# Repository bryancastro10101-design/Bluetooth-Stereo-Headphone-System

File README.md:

# 🎧 Bluetooth Stereo Headphone System
**EE 445L Embedded System Design Lab — Final Project | The University of Texas at Austin**

A fully functional wireless stereo audio system built from scratch using an ESP32 and TM4C123 microcontroller, featuring real-time DSP, dual TFT displays, and a custom PCB designed in KiCad.

---

## 📌 Project Overview

This project demonstrates end-to-end embedded system design — from hardware architecture and PCB layout to firmware development and digital signal processing. Audio is streamed wirelessly from a PC via Bluetooth (A2DP protocol), decoded by an ESP32, and transmitted over SPI to a TM4C123 microcontroller for processing and playback through dual speakers.

---

## 🏗️ System Architecture

```
[PC / Spotify]
     │
     │  Bluetooth A2DP
     ▼
[ESP32 DevKitC]  ──── SPI ────►  [TM4C123GH6PM]
                                       │
                          ┌────────────┴────────────┐
                          │                         │
                     [TLV5616 DAC]           [TLV5616 DAC]
                          │                         │
                    [MCP34119 OPA]           [MCP34119 OPA]
                          │                         │
                      [Speaker L]             [Speaker R]
                          
         [ST7735R LCD ×2]  ◄── SPI ── TM4C123
         [Volume Buttons ×4]
```

**Communication Protocols:**
- **Bluetooth A2DP** — Wireless audio streaming from PC to ESP32
- **SPI** — ESP32 → TM4C123 audio data transfer; TM4C123 → DACs and LCD screens
- **I2C** — ESP32 ↔ TM4C123 control/status channel

---

## ⚙️ Hardware Components

| Component | Part | Qty | Role |
|---|---|---|---|
| Microcontroller | TM4C123GH6PM | 1 | Main audio processor |
| Wireless MCU | ESP32-DevKitC-V4 | 1 | Bluetooth A2DP receiver |
| TFT Display | ST7735R | 2 | Real-time audio level UI |
| DAC | TLV5616 | 2 | Digital-to-analog conversion |
| Op-Amp | MCP34119P | 2 | Audio amplification |
| Buck Regulator | MPM3610GQV | 2 | 9V → 5V and 9V → 3.3V |
| Voltage Reference | LM4041CILPR | 1 | Stable DAC reference |

---

## 🔋 Power Budget

| Rail | Load Breakdown | Range |
|---|---|---|
| **3.3V** | TM4C123 + 2× ST7735R + ESP32 + regulators + Vref | 231 mA – 321 mA |
| **5V** | 2× MCP34119 + 2× TLV5616 | ~2.32 mA |

Both rails are supplied by MPM3610GQV switching regulators from a 9V source, chosen for their high efficiency and small footprint.

---

## 💻 Firmware Design

### ESP32 — Bluetooth Receiver
Receives audio data over Bluetooth A2DP and streams it to the TM4C123 via SPI as fast as data is available.

```c
// ESP32 pseudocode
int main() {
    while (true) {
        while (SoundDataReady) {
            SPIOut(SoundData);
        }
    }
    return 0;
}
```

### TM4C123 — Audio Processor
Acts as the SPI slave, processes incoming audio data, and distributes it to the two DAC channels and both LCD displays.

**Module structure:**
```
dac.h       → DAC_Init(), DAC_Output(uint16_t data)
slave.h     → Slave_Init(void (*handler)(uint8_t databyte))
speaker.h   → init_Speaker(), play_Sound(int soundData)
lcd.h       → init_LCD(), update_LCD(update_Params params)
```

---

## 🖥️ User Interface

- **2× ST7735R TFT displays** showing real-time audio level visualization that responds dynamically to volume
- **4 buttons** (2 per channel) for:
  - Volume control (up/down)
  - Equalization adjustment

---

## 📐 PCB Design

Designed in **KiCad** targeting **JLCPCB** manufacturing rules.

**Key design decisions:**
- Regulators placed close to the battery connector to minimize long power traces
- Speaker/Amp/DAC subcircuit routed once and mirrored for the stereo channel
- Booster pack headers spaced for TM4C123 LaunchPad compatibility
- Crystal oscillator isolated from high-speed signal traces

---

## 📊 Performance Targets

| Metric | Target |
|---|---|
| Frequency Response | 20 Hz – 20 kHz |
| SNR | ≥ 80 dB |
| Button Response Time | Measured via logic analyzer |
| Bluetooth Range | Up to ~10 m (Class 2) |

---

## 🛠️ Skills Demonstrated

- **Embedded C firmware** on ARM Cortex-M4 (TM4C123)
- **SPI/I2C protocol implementation** (master & slave)
- **Bluetooth A2DP** wireless audio protocol
- **Digital Signal Processing** — real-time audio equalization
- **PCB design** in KiCad (schematic capture, layout, DRC)
- **Analog circuit design** — DAC output stage with op-amp buffering
- **Power electronics** — switching regulator selection and layout
- **Hardware/software co-design** across two MCUs

---

## 📁 Repository Structure

```
├── firmware/
│   ├── esp32/          # Bluetooth A2DP receiver code
│   └── tm4c/           # Audio processor, DAC, LCD, SPI slave
├── hardware/
│   ├── schematic/      # KiCad schematic files
│   ├── pcb/            # KiCad PCB layout files
│   └── datasheets/     # Component datasheets
├── docs/
│   ├── system_diagram.pdf
│   ├── requirements_document.pdf
│   └── power_calculations.txt
└── README.md
```

---

## 🎓 Course Context

**EE 445L — Embedded Systems Design Lab**  
Department of Electrical and Computer Engineering  
The University of Texas at Austin

This course covers real-time embedded system design, hardware/software integration, and PCB prototyping with an emphasis on the full engineering design cycle from requirements through implementation and testing.

---

---

## 📝 Lessons Learned

The board flashed successfully with all components soldered — until the buck converters were added. Once the MPM3610GQV regulators were populated, the board could no longer be programmed via JTAG.

After consulting with other engineers, the team's leading hypothesis is **switching noise crosstalk from the buck converters into the JTAG lines**. The regulators were placed in relative proximity to the JTAG header on a 2-layer PCB, which lacks the dedicated ground and power planes of a 4-layer design. Without those inner planes acting as a Faraday shield and low-impedance return path, the high-frequency switching transients generated by the regulators likely coupled into the JTAG data lines and disrupted the debug interface.

The audio side had its own surprise as well. One of the external ADC converters was producing noticeably poor sound quality that we couldn't tune out. Rather than spin a new board, the team jumped a wire on the back of the PCB to bypass it and route the signal directly into the ESP32's onboard ADC instead — which performed considerably better. It wasn't pretty, but it worked, and the project stayed on schedule. A classic embedded engineering field fix.

**Key takeaways for future designs:**
- Move to a **4-layer stackup** (signal / ground / power / signal) to provide shielding and clean return paths — especially important when mixing switching regulators with sensitive digital interfaces
- Increase the **physical separation** between switching regulators and JTAG/SWD headers, and avoid routing debug lines near regulator switching nodes
- Add **bulk and bypass capacitance** close to the regulator output to suppress switching noise at the source
- Consider adding a **ferrite bead or LC filter** on the power rail feeding the microcontroller to further isolate debug circuitry from regulator noise

---

*Designed and implemented as part of the EE 445L final project. All schematics, firmware, and documentation produced independently.*

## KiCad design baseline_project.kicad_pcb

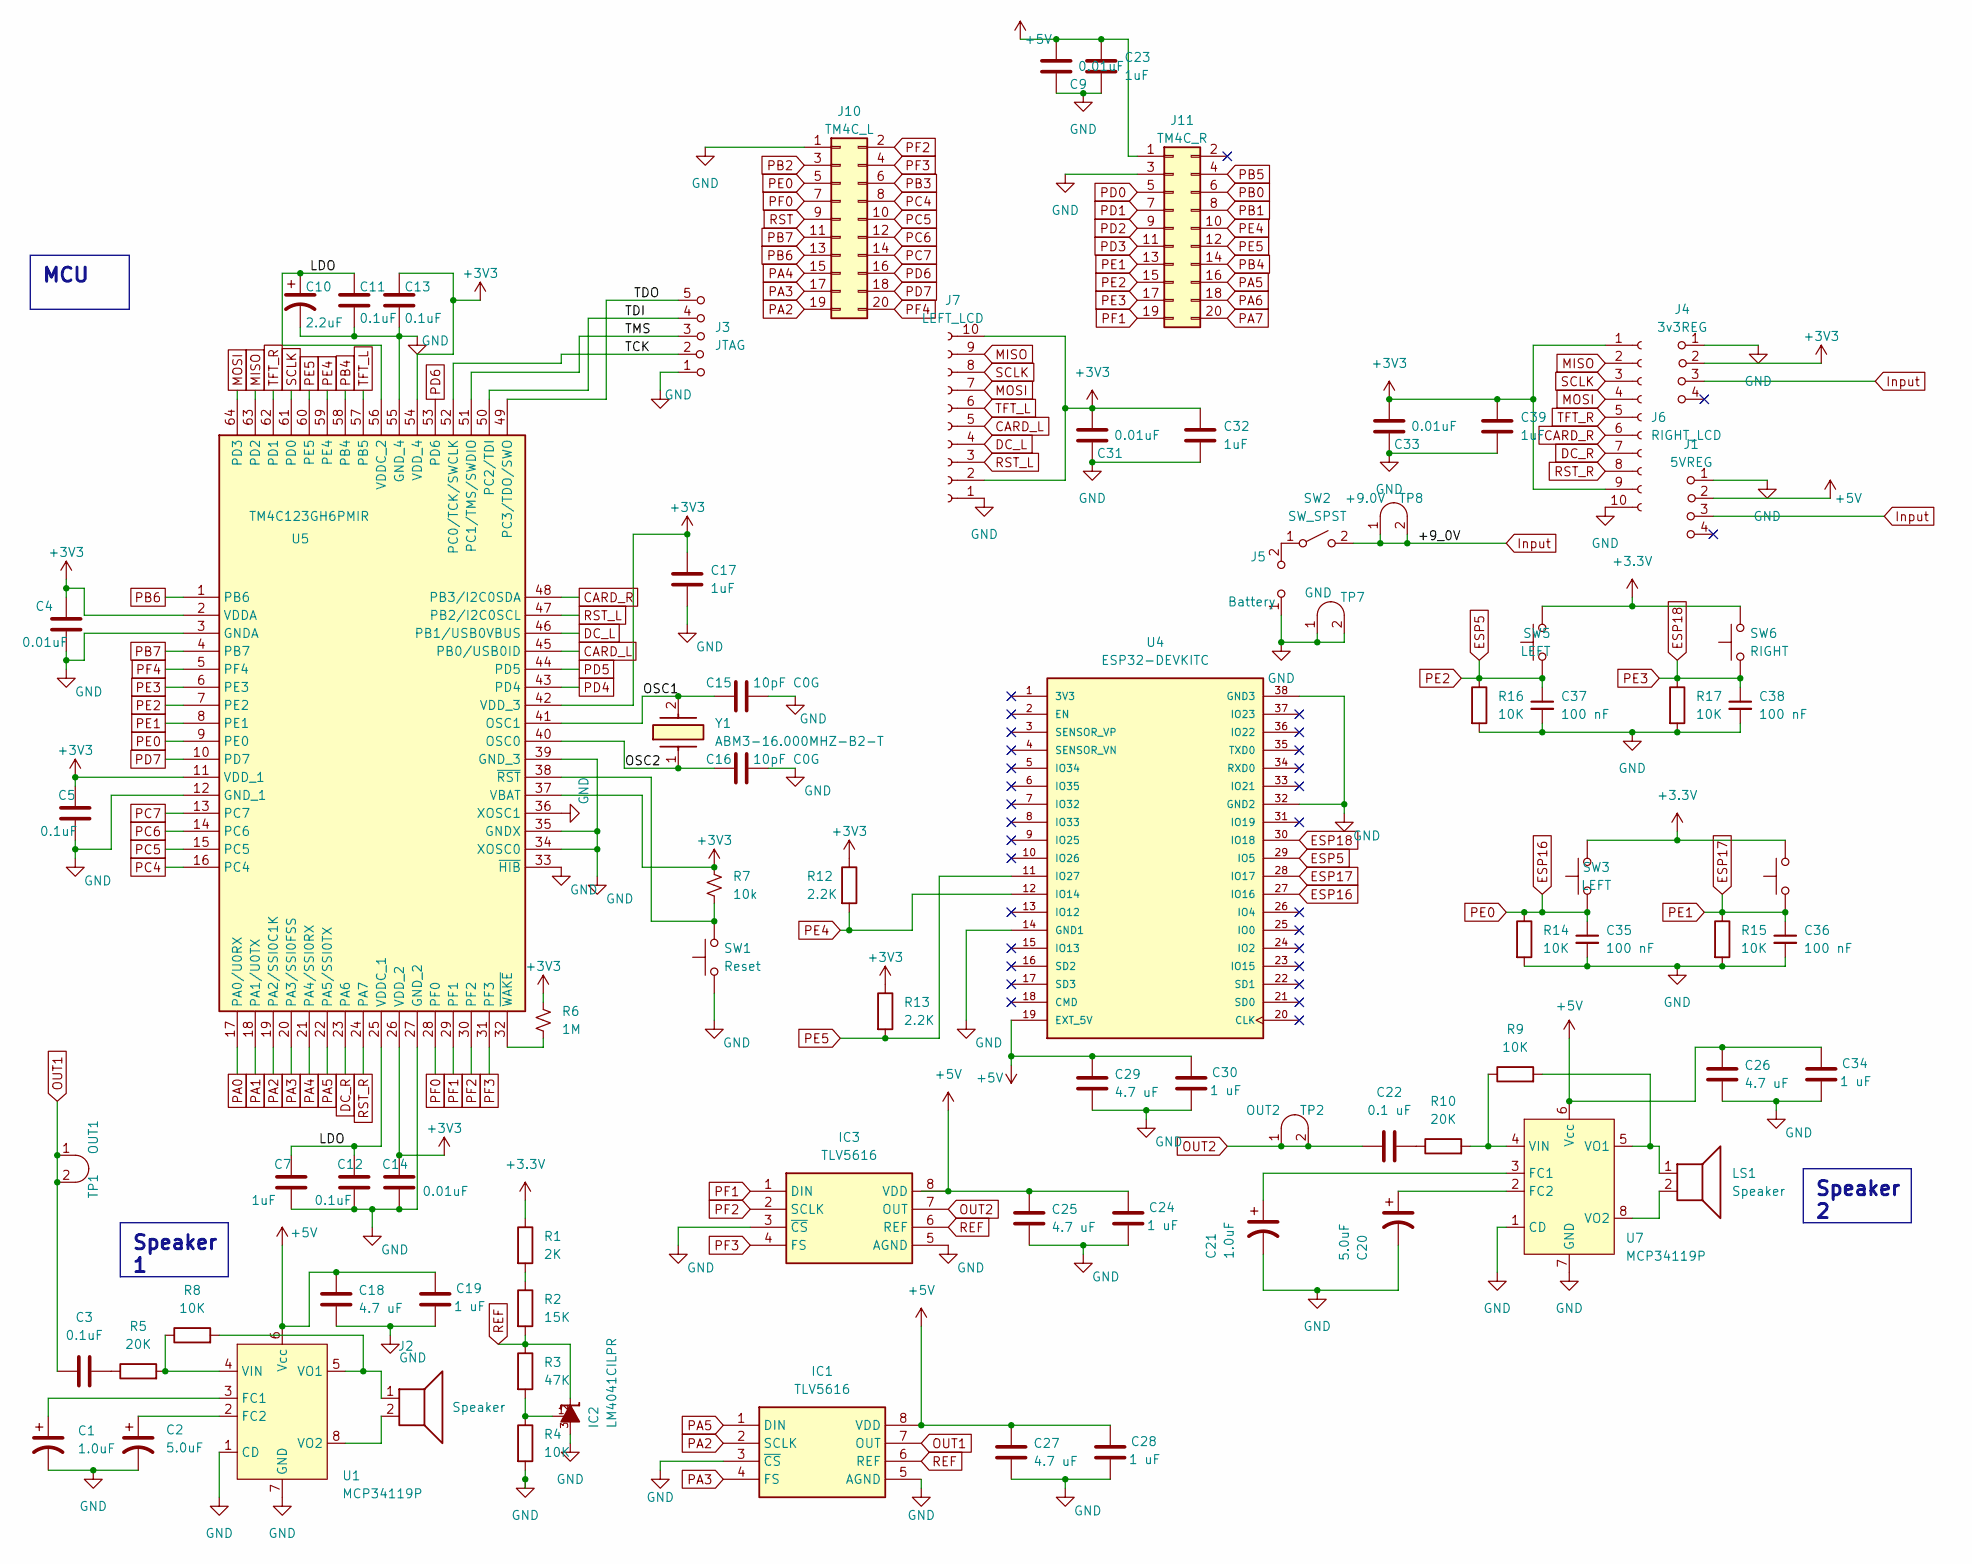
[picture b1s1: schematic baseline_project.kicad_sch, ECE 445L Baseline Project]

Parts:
C1, C21: 1.0uF; CP_Radial_Tantal200mil
C2, C20: 5.0uF; CP_Radial_Tantal200mil
C3, C5, C11, C12, C13: 0.1uF; C_Axial_200mil
C4, C9, C14, C31, C33: 0.01uF; C_Axial_200mil
C7, C17, C23, C32, C39: 1uF; C_Axial_200mil
C10: 2.2uF; CP_Radial_Tantal200mil
C15, C16: 10pF C0G; C_Axial_200mil
C18, C25, C26, C27, C29: 4.7 uF; C_Axial_200mil
C19, C24, C28, C30, C34: 1 uF; C_Axial_200mil
C22: 0.1 uF; C_Axial_200mil
C35, C36, C37, C38: 100 nF; C_Axial_200mil
IC1, IC3: TLV5616; DIP-8_W7.62mm_LongPads
IC2: LM4041CILPR; ti_LM4041CILPR
J1: 5VREG; PinHeader_1x04_P2.54mm_Vertical
J2: Speaker; PinHeader_1x02_P2.54mm_Vertical
J3: JTAG; PinHeader_1x05_P2.54mm_Vertical
J4: 3v3REG; PinHeader_1x04_P2.54mm_Vertical
J5: Battery; PinHeader_1x02_P2.54mm_Vertical
J6: RIGHT_LCD; PinHeader_1x10_P2.54mm_Vertical
J7: LEFT_LCD; PinHeader_1x10_P2.54mm_Vertical
J10: TM4C_L; PinSocket_2x10_P2.54mm_Vertical
J11: TM4C_R; PinSocket_2x10_P2.54mm_Vertical
LS1: Speaker; PinHeader_1x02_P2.54mm_Vertical
R1: 2K; R_Axial_DIN0204_L3.6mm_D1.6mm_P7.62mm_Horizontal
R2: 15K; R_Axial_DIN0204_L3.6mm_D1.6mm_P7.62mm_Horizontal
R3: 47K; R_Axial_DIN0204_L3.6mm_D1.6mm_P7.62mm_Horizontal
R4, R8, R9, R14, R15, R16, R17: 10K; R_Axial_DIN0204_L3.6mm_D1.6mm_P7.62mm_Horizontal
R5, R10: 20K; R_Axial_DIN0204_L3.6mm_D1.6mm_P7.62mm_Horizontal
R6: 1M; R_Axial_DIN0204_L3.6mm_D1.6mm_P7.62mm_Horizontal
R7: 10k; R_Axial_DIN0204_L3.6mm_D1.6mm_P7.62mm_Horizontal
R12, R13: 2.2K; R_Axial_DIN0204_L3.6mm_D1.6mm_P7.62mm_Horizontal
SW1: Reset; SW_PUSH_6mm
SW2: SW_SPST; SW_DIP_SPSTx01_Slide_9.78x4.72mm_W7.62mm_P2.54mm
SW3, SW5: LEFT; SW_PUSH_6mm
SW4, SW6: RIGHT; SW_PUSH_6mm
TP1: OUT1; Testpoint_1x02_P2.54mm
TP2: OUT2; Testpoint_1x02_P2.54mm
TP7: GND; Testpoint_1x02_P2.54mm
TP8: +9.0V; Testpoint_1x02_P2.54mm
U1, U7: MCP34119P; DIP-8_W7.62mm_LongPads
U4: ESP32-DEVKITC; MODULE_ESP32-DEVKITC; PARTREV N/A
U5: TM4C123GH6PMIR; QFP50P1200X1200X160-64N; Mouser Part Number 595-TM4C123GH6PMIR
Y1: ABM3-16.000MHZ-B2-T; ABM3; Mouser Part Number 815-ABM3-16-B2-T

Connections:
+3.3V: R1.1, SW3.2, SW4.2, SW5.2, SW6.2
+3V3: C4.1, C5.1, C13.1, C14.1, C17.1, C31.2, C32.1, C33.2, C39.1, J4.2 (B), J6.1, J6.9, J7.2, J7.10, R6.1, R7.1, R12.1, R13.1, U5.2 (VDDA), U5.11 (VDD_1), U5.26 (VDD_2), U5.37 (VBAT), U5.42 (VDD_3), U5.54 (VDD_4); also elsewhere on the board
+5V: C9.2, C18.2, C19.2, C23.1, C24.2, C25.2, C26.2, C27.2, C28.2, C29.2, C30.2, C34.2, IC1.8 (VDD), IC3.8 (VDD), J1.2 (B), J11.1, U1.6 (Vcc), U4.19 (EXT_5V), U7.6 (Vcc); also elsewhere on the board
/LDO: C7.1, C10.1, C11.1, C12.1, U5.25 (VDDC_1), U5.56 (VDDC_2)
/OSC1: C15.1, U5.41 (OSC1), Y1.2
/OSC2: C16.1, U5.40 (OSC0), Y1.1
/TCK: J3.2 (B), U5.52 (PC0/TCK/SWCLK); also elsewhere on the board
/TDI: J3.4 (C), U5.50 (PC2/TDI); also elsewhere on the board
/TDO: J3.5 (C), U5.49 (PC3/TDO/SWO); also elsewhere on the board
/TMS: J3.3 (C), U5.51 (PC1/TMS/SWDIO); also elsewhere on the board
CARD_L: J7.5, U5.45 (PB0/USB0ID); also elsewhere on the board
CARD_R: J6.6, U5.48 (PB3/I2C0SDA); also elsewhere on the board
DC_L: J7.4, U5.46 (PB1/USB0VBUS); also elsewhere on the board
DC_R: J6.7, U5.23 (PA6); also elsewhere on the board
ESP5: C37.1, J11.15, R16.1, SW5.1, U4.29 (IO5), U5.7 (PE2); also elsewhere on the board
ESP16: C35.1, J10.5, R14.1, SW3.1, U4.27 (IO16), U5.9 (PE0); also elsewhere on the board
ESP17: C36.1, J11.13, R15.1, SW4.1, U4.28 (IO17), U5.8 (PE1); also elsewhere on the board
ESP18: C38.1, J11.17, R17.1, SW6.1, U4.30 (IO18), U5.6 (PE3); also elsewhere on the board
GND: C1.2, C2.2, C4.2, C5.2, C7.2, C9.1, C10.2, C11.2, C12.2, C13.2, C14.2, C15.2, C16.2, C17.2, C18.1, C19.1, C20.2, C21.2, C23.2, C24.1, C25.1, C26.1, C27.1, C28.1, C29.1, C30.1, C31.1, C32.2, C33.1, C34.1, C35.2, C36.2, C37.2, C38.2, C39.2, IC1.3 (~CS), IC1.5 (AGND), IC2.3, IC3.3 (~CS), IC3.5 (AGND), J1.1 (A), J3.1 (A), J4.1 (A), J5.1 (A), J6.10, J7.1, J10.1, J11.3, R4.2, R14.2, R15.2, R16.2, R17.2, SW1.1, TP7.1 (A), TP7.2 (B), U1.1 (CD), U1.7 (GND), U4.14 (GND1), U4.32 (GND2), U4.38 (GND3), U5.3 (GNDA), U5.12 (GND_1), U5.27 (GND_2), U5.33 (~HIB), U5.34 (XOSC0), U5.35 (GNDX), U5.36 (XOSC1), U5.39 (GND_3), U5.55 (GND_4), U7.1 (CD), U7.7 (GND); also elsewhere on the board
Input: J1.3 (C), J4.3 (C), SW2.2 (B), TP8.1 (A), TP8.2 (B)
MISO: J6.2, J7.9, U5.63 (PD2); also elsewhere on the board
MOSI: J6.4, J7.7, U5.64 (PD3); also elsewhere on the board
unnamed: C3.2, R5.1
unnamed: C22.2, R10.1
unnamed: IC2.1, R3.2, R4.1
unnamed: J5.2 (B), SW2.1 (A)
unnamed: R1.2, R2.1
unnamed: C1.1, U1.3 (FC1)
unnamed: C2.1, U1.2 (FC2)
unnamed: R5.2, R8.1, U1.4 (VIN)
unnamed: J2.1, R8.2, U1.5 (VO1)
unnamed: J2.2, U1.8 (VO2)
unnamed: R7.2, SW1.2, U5.38 (~RST)
unnamed: R6.2, U5.32 (~WAKE)
unnamed: C21.1, U7.3 (FC1)
unnamed: C20.1, U7.2 (FC2)
unnamed: R9.1, R10.2, U7.4 (VIN)
unnamed: LS1.1, R9.2, U7.5 (VO1)
unnamed: LS1.2, U7.8 (VO2)
OUT1: C3.1, IC1.7 (OUT), TP1.1 (A), TP1.2 (B)
OUT2: C22.1, IC3.7 (OUT), TP2.1 (A), TP2.2 (B)
PA0: U5.17 (PA0/U0RX)
PA1: U5.18 (PA1/U0TX)
PA2: IC1.2 (SCLK), J10.19, U5.19 (PA2/SSI0C1K); also elsewhere on the board
PA3: IC1.4 (FS), J10.17, U5.20 (PA3/SSI0FSS); also elsewhere on the board
PA4: J10.15, U5.21 (PA4/SSI0RX); also elsewhere on the board
PA5: IC1.1 (DIN), J11.16, U5.22 (PA5/SSI0TX); also elsewhere on the board
PB4: J11.14, U5.58 (PB4); also elsewhere on the board
PB6: J10.13, U5.1 (PB6); also elsewhere on the board
PB7: J10.11, U5.4 (PB7); also elsewhere on the board
PC4: J10.8, U5.16 (PC4); also elsewhere on the board
PC5: J10.10, U5.15 (PC5); also elsewhere on the board
PC6: J10.12, U5.14 (PC6); also elsewhere on the board
PC7: J10.14, U5.13 (PC7); also elsewhere on the board
PD4: U5.43 (PD4)
PD5: U5.44 (PD5)
PD6: J10.16, U5.53 (PD6); also elsewhere on the board
PD7: J10.18, U5.10 (PD7); also elsewhere on the board
PE4: J11.10, R12.2, U4.12 (IO14), U5.59 (PE4); also elsewhere on the board
PE5: J11.12, R13.2, U4.11 (IO27), U5.60 (PE5); also elsewhere on the board
PF0: J10.7, U5.28 (PF0); also elsewhere on the board
PF1: IC3.1 (DIN), J11.19, U5.29 (PF1); also elsewhere on the board
PF2: IC3.2 (SCLK), J10.2, U5.30 (PF2); also elsewhere on the board
PF3: IC3.4 (FS), J10.4, U5.31 (PF3); also elsewhere on the board
PF4: J10.20, U5.5 (PF4); also elsewhere on the board
REF: IC1.6 (REF), IC2.2, IC3.6 (REF), R2.2, R3.1
RST_L: J7.3, U5.47 (PB2/I2C0SCL); also elsewhere on the board
RST_R: J6.8, U5.24 (PA7); also elsewhere on the board
SCLK: J6.3, J7.8, U5.61 (PD0); also elsewhere on the board
TFT_L: J7.6, U5.57 (PB5); also elsewhere on the board
TFT_R: J6.5, U5.62 (PD1); also elsewhere on the board

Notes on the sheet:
MCU
Speaker 2
Speaker 1

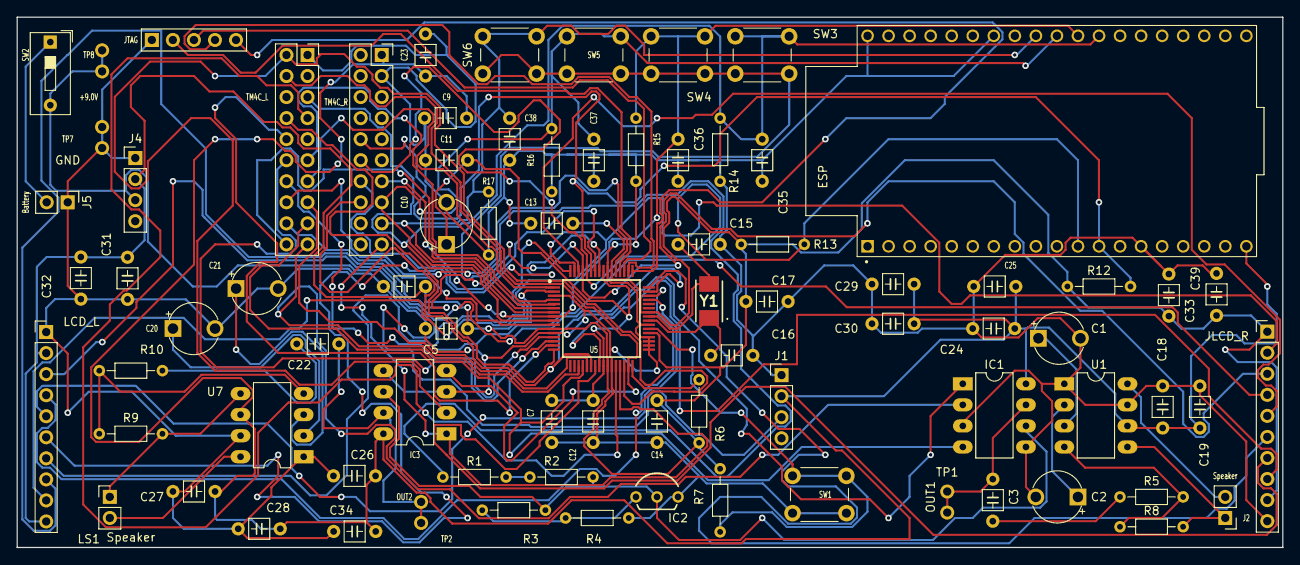
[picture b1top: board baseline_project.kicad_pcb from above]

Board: 2 copper layers, 152.8 x 64.0 mm, 81 parts (0 on the bottom side), 67 nets.

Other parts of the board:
ESP: ESP32-DEVKITC; MODULE_ESP32-DEVKITC
JLCD_R: RIGHT_LCD; PinHeader_1x10_P2.54mm_Vertical
JTAG: JTAG; PinHeader_1x05_P2.54mm_Vertical
LCD_L: LEFT_LCD; PinHeader_1x10_P2.54mm_Vertical
TM4C_L: TM4C_L; PinSocket_2x10_P2.54mm_Vertical
TM4C_R: TM4C_R; PinSocket_2x10_P2.54mm_Vertical

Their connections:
+3V3: JLCD_R.1, JLCD_R.9, LCD_L.2, LCD_L.10; also elsewhere on the board
+5V: ESP.19 (EXT_5V), TM4C_R.1; also elsewhere on the board
/TCK: JTAG.2 (B); also elsewhere on the board
/TDI: JTAG.4 (C); also elsewhere on the board
/TDO: JTAG.5 (C); also elsewhere on the board
/TMS: JTAG.3 (C); also elsewhere on the board
CARD_L: LCD_L.5; also elsewhere on the board
CARD_R: JLCD_R.6; also elsewhere on the board
DC_L: LCD_L.4; also elsewhere on the board
DC_R: JLCD_R.7; also elsewhere on the board
ESP5: ESP.29 (IO5), TM4C_R.15; also elsewhere on the board
ESP16: ESP.27 (IO16), TM4C_L.5; also elsewhere on the board
ESP17: ESP.28 (IO17), TM4C_R.13; also elsewhere on the board
ESP18: ESP.30 (IO18), TM4C_R.17; also elsewhere on the board
GND: ESP.14 (GND1), ESP.32 (GND2), ESP.38 (GND3), JLCD_R.10, JTAG.1 (A), LCD_L.1, TM4C_L.1, TM4C_R.3; also elsewhere on the board
MISO: JLCD_R.2, LCD_L.9; also elsewhere on the board
MOSI: JLCD_R.4, LCD_L.7; also elsewhere on the board
PA2: TM4C_L.19; also elsewhere on the board
PA3: TM4C_L.17; also elsewhere on the board
PA4: TM4C_L.15; also elsewhere on the board
PA5: TM4C_R.16; also elsewhere on the board
PB4: TM4C_R.14; also elsewhere on the board
PB6: TM4C_L.13; also elsewhere on the board
PB7: TM4C_L.11; also elsewhere on the board
PC4: TM4C_L.8; also elsewhere on the board
PC5: TM4C_L.10; also elsewhere on the board
PC6: TM4C_L.12; also elsewhere on the board
PC7: TM4C_L.14; also elsewhere on the board
PD6: TM4C_L.16; also elsewhere on the board
PD7: TM4C_L.18; also elsewhere on the board
PE4: ESP.12 (IO14), TM4C_R.10; also elsewhere on the board
PE5: ESP.11 (IO27), TM4C_R.12; also elsewhere on the board
PF0: TM4C_L.7; also elsewhere on the board
PF1: TM4C_R.19; also elsewhere on the board
PF2: TM4C_L.2; also elsewhere on the board
PF3: TM4C_L.4; also elsewhere on the board
PF4: TM4C_L.20; also elsewhere on the board
RST_L: LCD_L.3; also elsewhere on the board
RST_R: JLCD_R.8; also elsewhere on the board
SCLK: JLCD_R.3, LCD_L.8; also elsewhere on the board
TFT_L: LCD_L.6; also elsewhere on the board
TFT_R: JLCD_R.5; also elsewhere on the board

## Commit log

2026-02-23 Revise README for Bluetooth Stereo Headphone System
    Updated README to enhance project description and structure.
